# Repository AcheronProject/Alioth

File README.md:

# Acheron Alioth PCB

See [this page](https://gondolindrim.github.io/AcheronDocs/alioth/intro.html) for the Alioth documentation.

# Features

Alioth is an open-source replacement PCB for the Polaris keyboard. It is powered by an STM32F072 MCU and supports a big array of layout options, including:

- Full and split backspace
- Full and split right shift
- ANSI and ISO options
- Stepped caps lock

Alioth also features:

- Per-key single color LEDs
- Flex or relief cuts
- USBC connection
- QMK firmware compatibility

# Pictures

Yet not available as of june 25, 2020.

# Plate files

In the __polaris_plates__ folder there are the KiCad files for the ANSI and ISO versions of the half and full plates of the Polaris. These files can be submitted to a PCB manufacturer such as Elecrow to be manufactured in FR4 material. There are also SVG vectorized files which can be used to produce these plates in any other material.

# Licensing

Alioth is released under the Acheron Open-Hardware License AOHL version 1.3; see the __LICENSE.md__ file included in the root folder of this repository. However, the files in the ``polaris_resources`` folder were not authored by the Acheron Project but by the original Polaris PCB designer, ai03, and as such are subject to their own licensing. These files were obtained by Gondolindrim from [ai03's public repository](http://dl.ai03.me) in June 24, 2020. These files are licensed under the __README.txt__ file in the __polaris_resources__ folder. For commercial use of the files, please contact ai03 directly. Even with this license, permission to use these files to design the replacement Alioth PCB was given from ai03 to Gondolindrim expressly.

Commercial use of this PCB is licensed under the AOHL 1.3, but it would be a good idea to contact ai03 since the Polaris is a KBDFans product.

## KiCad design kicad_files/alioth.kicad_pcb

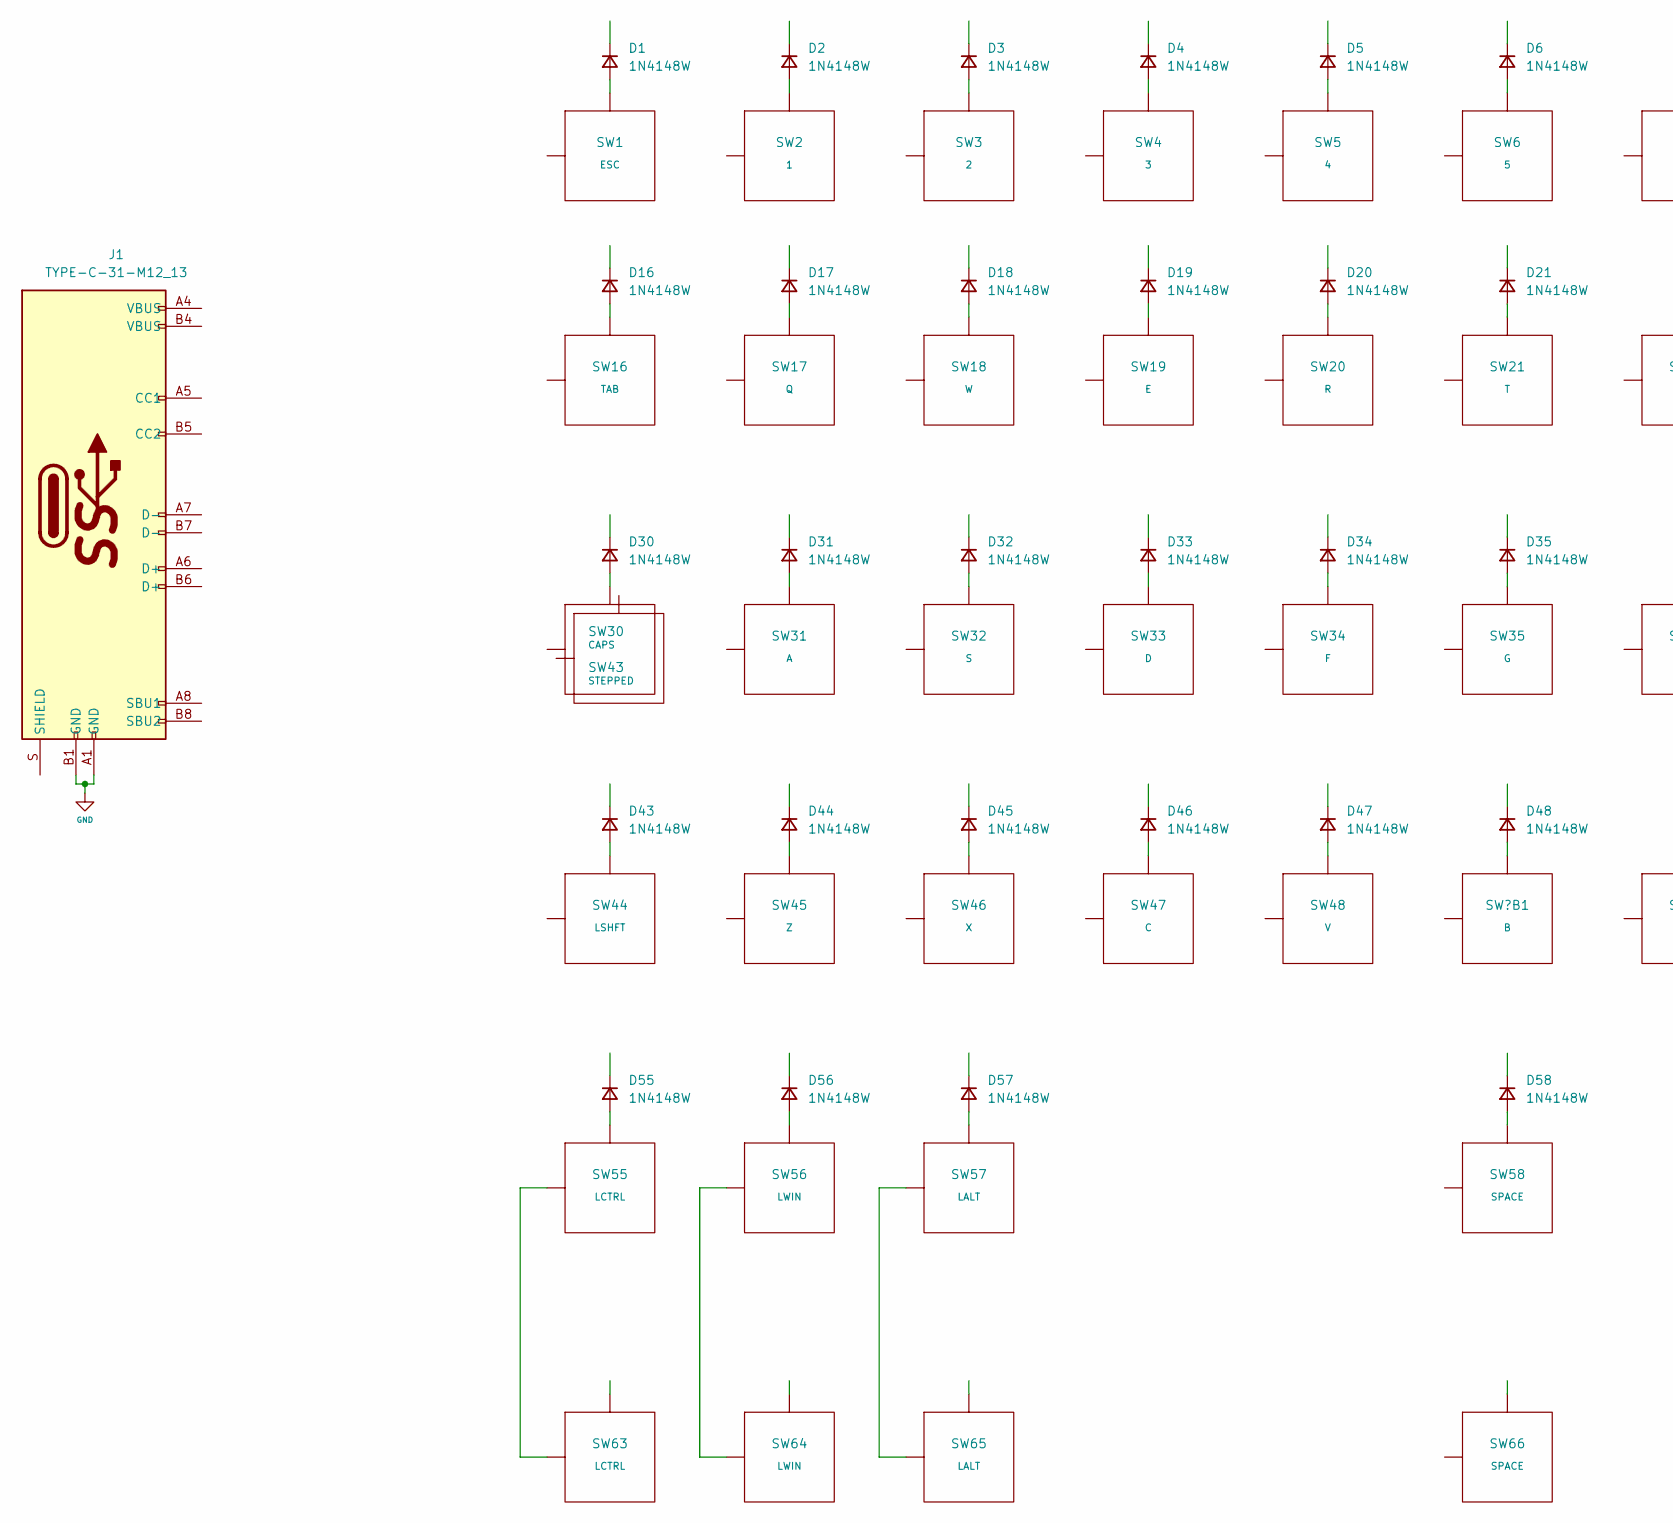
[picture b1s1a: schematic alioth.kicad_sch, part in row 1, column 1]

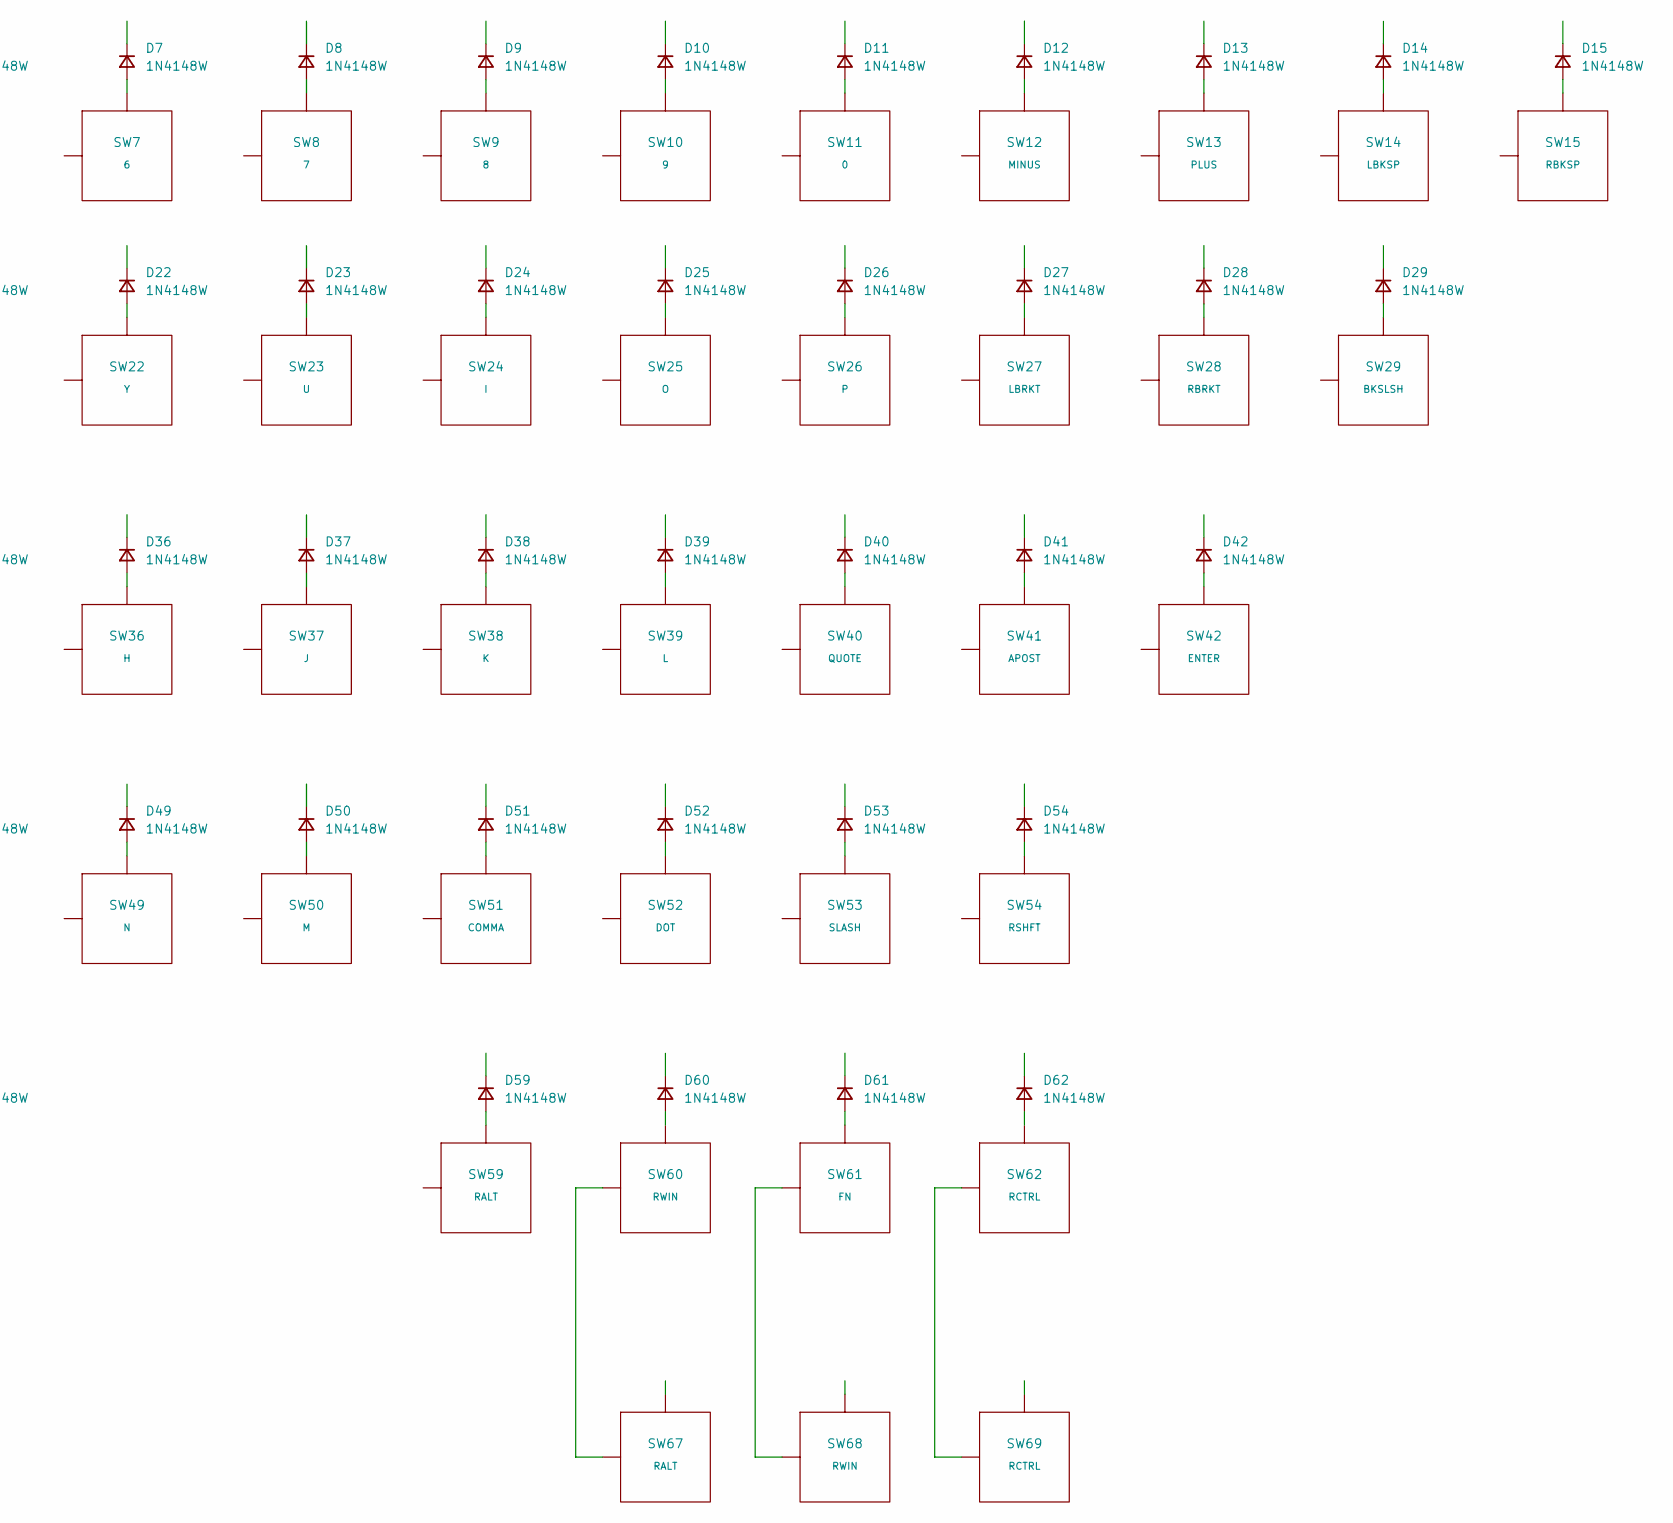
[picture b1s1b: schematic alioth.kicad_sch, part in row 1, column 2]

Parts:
D1, D2, D3, D4, D5, D6, D7, D8, D9, D10, D11, D12, D13, D14, D15, D16, D17, D18, D19, D20, D21, D22, D23, D24, D25, D26, D27, D28, D29, D30, D31, D32, D33, D34, D35, D36, D37, D38, D39, D40, D41, D42, D43, D44, D45, D46, D47, D48, D49, D50, D51, D52, D53, D54, D55, D56, D57, D58, D59, D60, D61, D62: 1N4148W; D_SOD-123
J1: TYPE-C-31-M12_13; TYPE-C-31-M-12
SW1: ESC; MX100
SW2: 1; MX100
SW3: 2; MX100
SW4: 3; MX100
SW5: 4; MX100
SW6: 5; MX100
SW7: 6; MX100
SW8: 7; MX100
SW9: 8; MX100
SW10: 9; MX100
SW11: 0; MX100
SW12: MINUS; MX100
SW13: PLUS; MX100
SW14: LBKSP; MX100
SW15: RBKSP; MX100
SW16: TAB; MX150
SW17: Q; MX100
SW18: W; MX100
SW19: E; MX100
SW20: R; MX100
SW21: T; MX100
SW22: Y; MX100
SW23: U; MX100
SW24: I; MX100
SW25: O; MX100
SW26: P; MX100
SW27: LBRKT; MX100
SW28: RBRKT; MX100
SW29: BKSLSH; MX150
SW30: CAPS; MX175
SW31: A; MX100
SW32: S; MX100
SW33: D; MX100
SW34: F; MX100
SW35: G; MX100
SW36: H; MX100
SW37: J; MX100
SW38: K; MX100
SW39: L; MX100
SW40: QUOTE; MX100
SW41: APOST; MX100
SW42: ENTER; MX225R
SW43: STEPPED; MX125
SW44: LSHFT; MX225
SW45: Z; MX100
SW46: X; MX100
SW47: C; MX100
SW48: V; MX100
SW49: N; MX100
SW50: M; MX100
SW51: COMMA; MX100
SW52: DOT; MX100
SW53: SLASH; MX100
SW54: RSHFT; MX275
SW55: LCTRL; MX125
SW56: LWIN; MX125
SW57: LALT; MX125
SW58: SPACE; MX625R
SW59: RALT; MX125
SW60: RWIN; MX125
SW61: FN; MX125
SW62: RCTRL; MX125
SW63: LCTRL; MX150
SW64: LWIN; MX100
SW65: LALT; MX150
SW66: SPACE; MX700R
SW67: RALT; MX150
SW68: RWIN; MX100
SW69: RCTRL; MX150
SW?B1: B; MX100

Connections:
GND: J1.A1 (GND), J1.B1 (GND)
unnamed: D1.2 (A), SW1.2 (Row)
unnamed: D2.2 (A), SW2.2 (Row)
unnamed: D3.2 (A), SW3.2 (Row)
unnamed: D4.2 (A), SW4.2 (Row)
unnamed: D5.2 (A), SW5.2 (Row)
unnamed: D6.2 (A), SW6.2 (Row)
unnamed: D7.2 (A), SW7.2 (Row)
unnamed: D8.2 (A), SW8.2 (Row)
unnamed: D9.2 (A), SW9.2 (Row)
unnamed: D10.2 (A), SW10.2 (Row)
unnamed: D11.2 (A), SW11.2 (Row)
unnamed: D12.2 (A), SW12.2 (Row)
unnamed: D13.2 (A), SW13.2 (Row)
unnamed: D14.2 (A), SW14.2 (Row)
unnamed: D15.2 (A), SW15.2 (Row)
unnamed: D16.2 (A), SW16.2 (Row)
unnamed: D17.2 (A), SW17.2 (Row)
unnamed: D18.2 (A), SW18.2 (Row)
unnamed: D19.2 (A), SW19.2 (Row)
unnamed: D20.2 (A), SW20.2 (Row)
unnamed: D21.2 (A), SW21.2 (Row)
unnamed: D22.2 (A), SW22.2 (Row)
unnamed: D23.2 (A), SW23.2 (Row)
unnamed: D24.2 (A), SW24.2 (Row)
unnamed: D25.2 (A), SW25.2 (Row)
unnamed: D26.2 (A), SW26.2 (Row)
unnamed: D27.2 (A), SW27.2 (Row)
unnamed: D28.2 (A), SW28.2 (Row)
unnamed: D29.2 (A), SW29.2 (Row)
unnamed: D30.2 (A), SW30.2 (Row)
unnamed: D31.2 (A), SW31.2 (Row)
unnamed: D32.2 (A), SW32.2 (Row)
unnamed: D33.2 (A), SW33.2 (Row)
unnamed: D34.2 (A), SW34.2 (Row)
unnamed: D35.2 (A), SW35.2 (Row)
unnamed: D36.2 (A), SW36.2 (Row)
unnamed: D37.2 (A), SW37.2 (Row)
unnamed: D38.2 (A), SW38.2 (Row)
unnamed: D39.2 (A), SW39.2 (Row)
unnamed: D40.2 (A), SW40.2 (Row)
unnamed: D41.2 (A), SW41.2 (Row)
unnamed: D42.2 (A), SW42.2 (Row)
unnamed: D43.2 (A), SW44.2 (Row)
unnamed: D44.2 (A), SW45.2 (Row)
unnamed: D45.2 (A), SW46.2 (Row)
unnamed: D46.2 (A), SW47.2 (Row)
unnamed: D47.2 (A), SW48.2 (Row)
unnamed: D48.2 (A), SW?B1.2 (Row)
unnamed: D49.2 (A), SW49.2 (Row)
unnamed: D50.2 (A), SW50.2 (Row)
unnamed: D51.2 (A), SW51.2 (Row)
unnamed: D52.2 (A), SW52.2 (Row)
unnamed: D53.2 (A), SW53.2 (Row)
unnamed: D54.2 (A), SW54.2 (Row)
unnamed: D55.2 (A), SW55.2 (Row)
unnamed: D56.2 (A), SW56.2 (Row)
unnamed: D57.2 (A), SW57.2 (Row)
unnamed: D58.2 (A), SW58.2 (Row)
unnamed: D59.2 (A), SW59.2 (Row)
unnamed: D60.2 (A), SW60.2 (Row)
unnamed: D61.2 (A), SW61.2 (Row)
unnamed: D62.2 (A), SW62.2 (Row)
unnamed: SW55.1 (Col), SW63.1 (Col)
unnamed: SW56.1 (Col), SW64.1 (Col)
unnamed: SW57.1 (Col), SW65.1 (Col)
unnamed: SW60.1 (Col), SW67.1 (Col)
unnamed: SW61.1 (Col), SW68.1 (Col)
unnamed: SW62.1 (Col), SW69.1 (Col)

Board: 2 copper layers, 133 parts (0 on the bottom side), 69 nets, no tracks yet.

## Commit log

2020-06-25 Plate files and PCB first files
2020-06-25 Fixed license links
